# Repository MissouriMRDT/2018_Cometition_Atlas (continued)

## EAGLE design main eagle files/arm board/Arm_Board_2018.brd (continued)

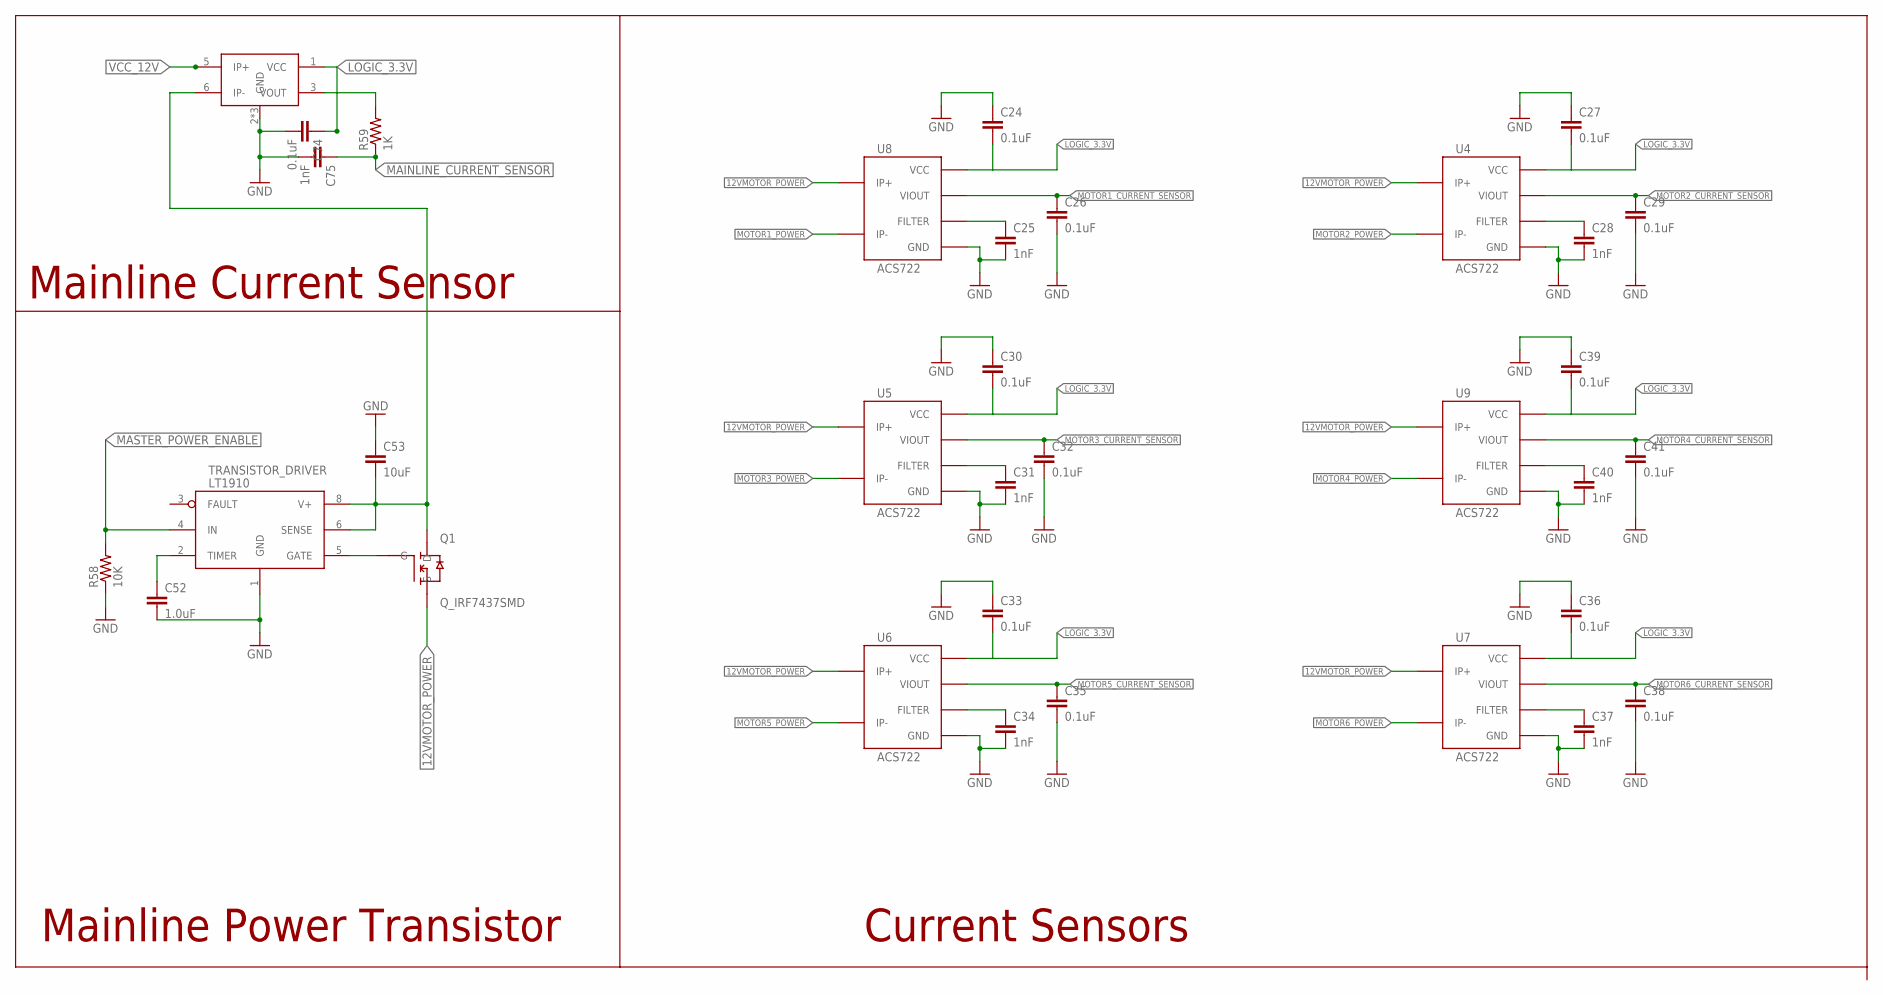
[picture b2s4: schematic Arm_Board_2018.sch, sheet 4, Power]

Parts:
C24, C26, C27, C29, C30, C32, C33, C35, C36, C38, C39, C41, C74: 0.1uF; 0603-CAP
C25, C28, C31, C34, C37, C40, C75: 1nF; 0603-CAP
C52: 1.0uF; 0603-CAP
C53: 10uF; 0603-CAP
MAINLINE_CURRENT: ACS781; 7-POWER_SMD_MODULE
Q1: Q_IRF7437SMD; D2PACK
R58: 10K; 0402-RES
R59: 1K; 0402-RES
TRANSISTOR_DRIVER: LT1910; SO8
U4, U5, U6, U7, U8, U9: ACS722; SOIC8

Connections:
12VMOTOR_POWER: Q1.2 (S), U4.1 (IP+), U4.2 (IP+), U5.1 (IP+), U5.2 (IP+), U6.1 (IP+), U6.2 (IP+), U7.1 (IP+), U7.2 (IP+), U8.1 (IP+), U8.2 (IP+), U9.1 (IP+), U9.2 (IP+); also elsewhere on the board
GND: C24.1, C25.2, C26.2, C27.1, C28.2, C29.2, C30.1, C31.2, C32.2, C33.1, C34.2, C35.2, C36.1, C37.2, C38.2, C39.1, C40.2, C41.2, C52.2, C53.1, C74.2, C75.2, MAINLINE_CURRENT.2 (GND), MAINLINE_CURRENT.4 (GND), MAINLINE_CURRENT.7 (GND), R58.1, TRANSISTOR_DRIVER.1 (GND), U4.5 (GND), U5.5 (GND), U6.5 (GND), U7.5 (GND), U8.5 (GND), U9.5 (GND); also elsewhere on the board
LOGIC_3.3V: C24.2, C27.2, C30.2, C33.2, C36.2, C39.2, C74.1, MAINLINE_CURRENT.1 (VCC), U4.8 (VCC), U5.8 (VCC), U6.8 (VCC), U7.8 (VCC), U8.8 (VCC), U9.8 (VCC); also elsewhere on the board
MAINLINE_CURRENT_SENSOR: C75.1, R59.1; also elsewhere on the board
MASTER_POWER_ENABLE: R58.2, TRANSISTOR_DRIVER.4 (IN); also elsewhere on the board
MOTOR1_CURRENT_SENSOR: C26.1, U8.7 (VIOUT); also elsewhere on the board
MOTOR1_POWER: U8.3 (IP-), U8.4 (IP-); also elsewhere on the board
MOTOR2_CURRENT_SENSOR: C29.1, U4.7 (VIOUT); also elsewhere on the board
MOTOR2_POWER: U4.3 (IP-), U4.4 (IP-); also elsewhere on the board
MOTOR3_CURRENT_SENSOR: C32.1, U5.7 (VIOUT); also elsewhere on the board
MOTOR3_POWER: U5.3 (IP-), U5.4 (IP-); also elsewhere on the board
MOTOR4_CURRENT_SENSOR: C41.1, U9.7 (VIOUT); also elsewhere on the board
MOTOR4_POWER: U9.3 (IP-), U9.4 (IP-); also elsewhere on the board
MOTOR5_CURRENT_SENSOR: C35.1, U6.7 (VIOUT); also elsewhere on the board
MOTOR5_POWER: U6.3 (IP-), U6.4 (IP-); also elsewhere on the board
MOTOR6_CURRENT_SENSOR: C38.1, U7.7 (VIOUT); also elsewhere on the board
MOTOR6_POWER: U7.3 (IP-), U7.4 (IP-); also elsewhere on the board
unnamed: C28.1, U4.6 (FILTER)
unnamed: C52.1, TRANSISTOR_DRIVER.2 (TIMER)
unnamed: C25.1, U8.6 (FILTER)
unnamed: C31.1, U5.6 (FILTER)
unnamed: C34.1, U6.6 (FILTER)
unnamed: C37.1, U7.6 (FILTER)
unnamed: C40.1, U9.6 (FILTER)
unnamed: Q1.1 (G), TRANSISTOR_DRIVER.5 (GATE)
unnamed: C53.2, MAINLINE_CURRENT.6 (IP-), Q1.TAB (D), TRANSISTOR_DRIVER.6 (SENSE), TRANSISTOR_DRIVER.8 (V+)
unnamed: MAINLINE_CURRENT.3 (VOUT), R59.2
VCC_12V: MAINLINE_CURRENT.5 (IP+); also elsewhere on the board

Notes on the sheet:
Current Sensors
Mainline Current Sensor
Mainline Power Transistor

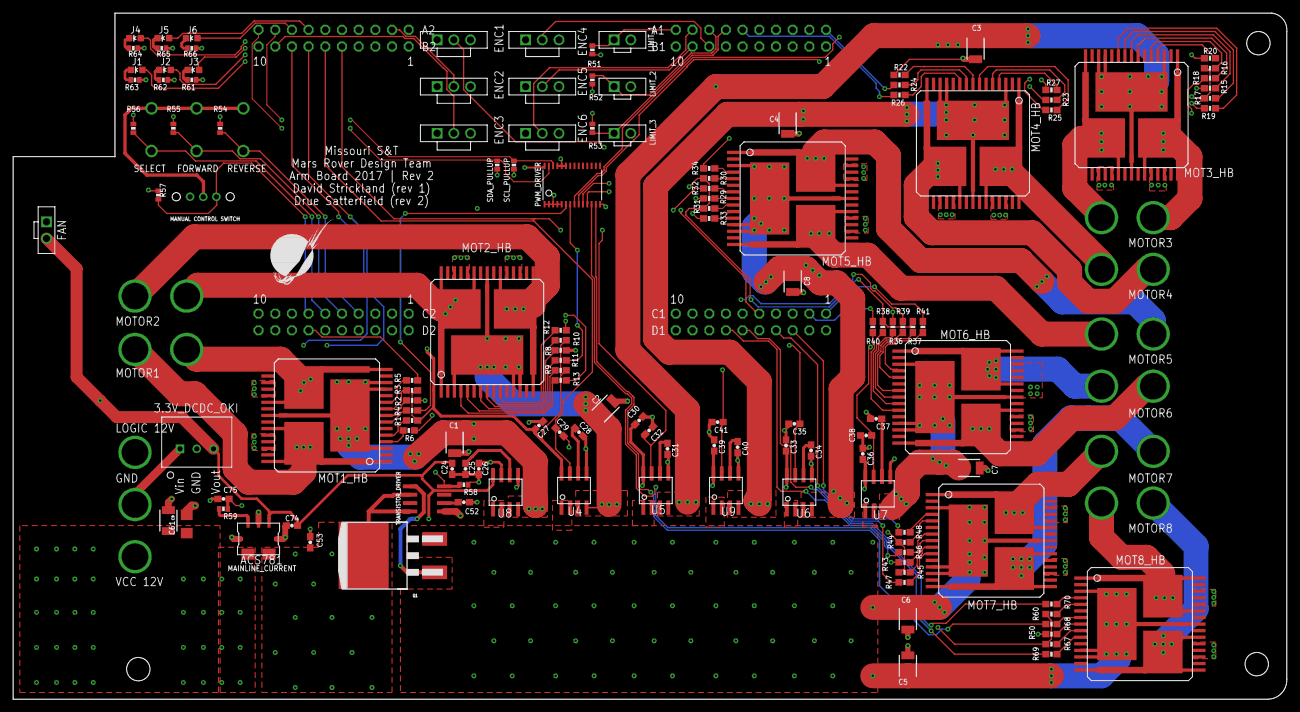
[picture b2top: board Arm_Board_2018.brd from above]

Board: 4 copper layers, 193.8 x 104.4 mm, 152 parts (0 on the bottom side), 144 nets.

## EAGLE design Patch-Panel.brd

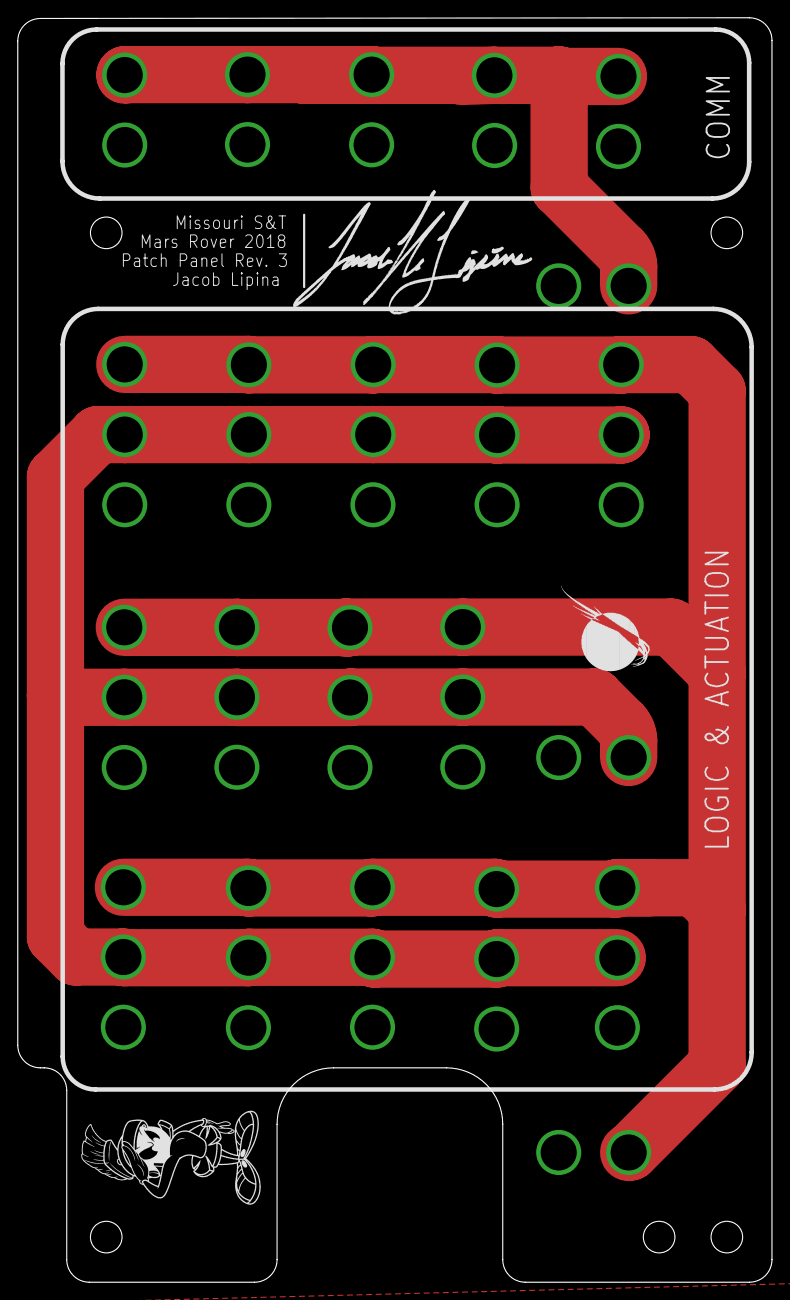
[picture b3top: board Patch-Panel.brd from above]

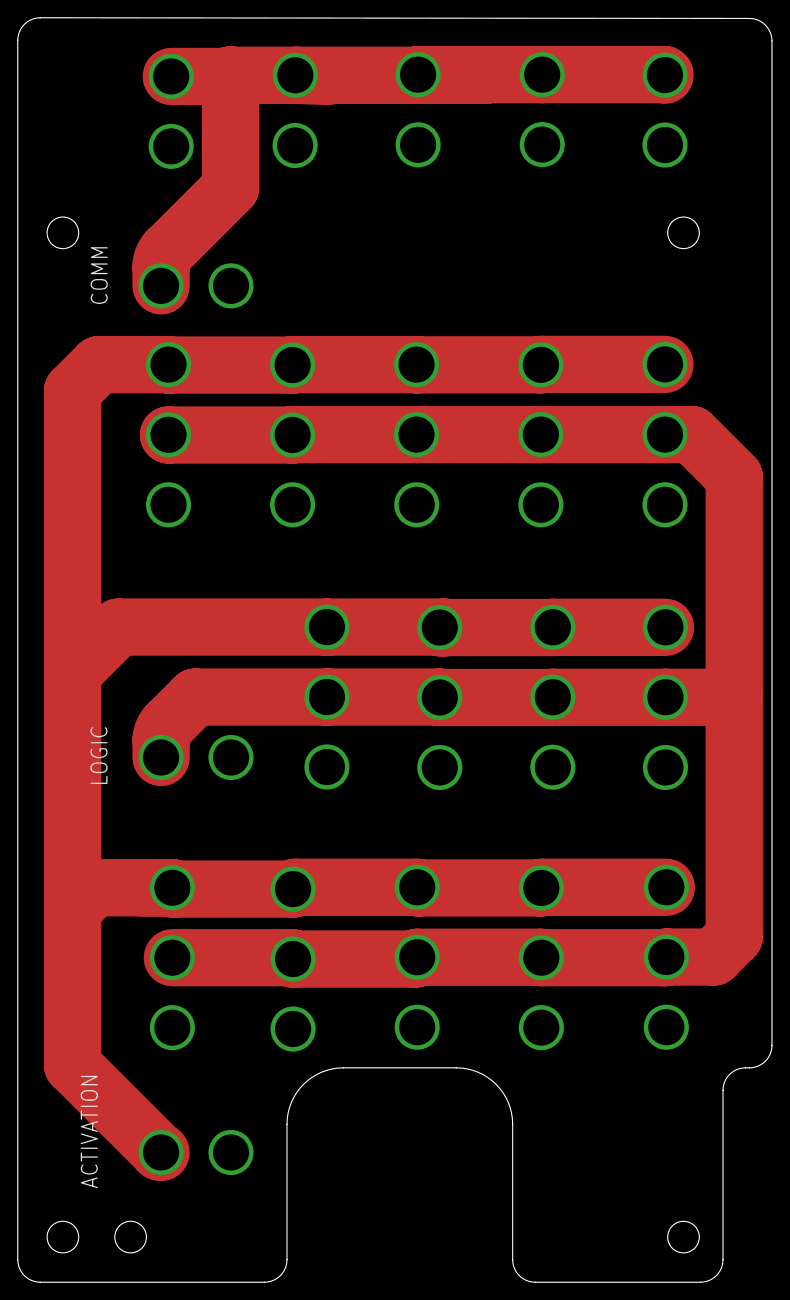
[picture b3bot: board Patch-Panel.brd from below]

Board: 2 copper layers, 84.9 x 142.3 mm, 66 parts (6 on the bottom side), 4 nets.

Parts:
H3, H4, H5, H6, H7: MOUNTING_HOLE#6; #6_SCREW
J1, J2, J3, J4, J5, J6, J7, J8, J9, J10, J11, J12, J13, J14, J15, J16, J17, J18, J19, J20, J21, J22, J23, J24, J25, J26, J27, J28, J29, J30, J31, J32, J33, J34, J35, J36, J37, J38, J39, J40, J41, J42, J43, J44, J45, J46, J47, J48, J49, J50, J51, J52, J53, J54, J55, J56, J57, J58: APPPP45_PCB_VERT; APP45_PCB_VERT
LOGO1: MRDT_LOGO
U$1: JACOB_SIG
U$2: MARVIN-THE-MARTIAN; MARVIN

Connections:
ACT-12V: J1.P$1, J9.P$1, J12.P$1, J15.P$1, J18.P$1, J21.P$1, J24.P$1, J27.P$1, J38.P$1, J41.P$1, J46.P$1, J49.P$1, J52.P$1, J55.P$1, J58.P$1
COM-12V: J5.P$1, J28.P$1, J30.P$1, J32.P$1, J34.P$1, J44.P$1
GND: J2.P$1, J4.P$1, J6.P$1, J7.P$1, J10.P$1, J13.P$1, J16.P$1, J19.P$1, J22.P$1, J25.P$1, J29.P$1, J31.P$1, J33.P$1, J35.P$1, J36.P$1, J39.P$1, J42.P$1, J45.P$1, J47.P$1, J50.P$1, J53.P$1, J56.P$1
LOG-12V: J3.P$1, J8.P$1, J11.P$1, J14.P$1, J17.P$1, J20.P$1, J23.P$1, J26.P$1, J37.P$1, J40.P$1, J43.P$1, J48.P$1, J51.P$1, J54.P$1, J57.P$1

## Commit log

2018-07-13 IK-ModelDevelopment
2018-07-13 GimbalBoard Software
2018-07-13 ScienceSattelite-Hardware
2018-07-13 RoveWare
2018-07-13 RoveBoard
2018-07-13 BmsBoardSoftware
2018-07-13 PowerBoardSoftware
2018-07-13 SensorPodSoftware
2018-07-13 NavBoardSoftware
2018-07-13 DrillBoardSoftware
2018-07-13 DriveBoardSoftware
2018-07-13 ScienceBoardSoftware
2018-07-13 ArmBoardSoftware
2018-07-13 AutonomyBoard-Software
2018-07-13 RoveWareEnergia
2018-07-13 CameraBoarSoftware
2018-07-13 SensorPod-Hardware
2018-07-13 CameraBoardHardware
2018-07-13 ArmBoardHardware
2018-07-13 DriveBoardhardware
2018-07-13 DrillBoard-Hardware
2018-07-13 NavBoard-Hardware
2018-07-13 KiCAD-Libraries-Hardware
2018-07-13 BMS-Charger-Hardware
2018-07-13 LEDPodBoadHardware
2018-07-13 ScienceBoard-ardware
2018-07-13 RoveBoardESP8266
2018-07-13 Power-Patch-Panel-Hardware
2018-07-13 PowerBoard-Hardware
2018-07-13 Motor-Controller-Hardware
2018-07-13 Eagle-Libraries-Hardware
2018-07-23 Drue's Modifications
2018-07-23 updated NavBoard
2019-03-25 Removed unnecesary motorware
2019-07-07 Update README.md
    added documentation on merging branches with commit history
2019-07-07 fixed numbering
2019-07-09 Removed depricated systems
